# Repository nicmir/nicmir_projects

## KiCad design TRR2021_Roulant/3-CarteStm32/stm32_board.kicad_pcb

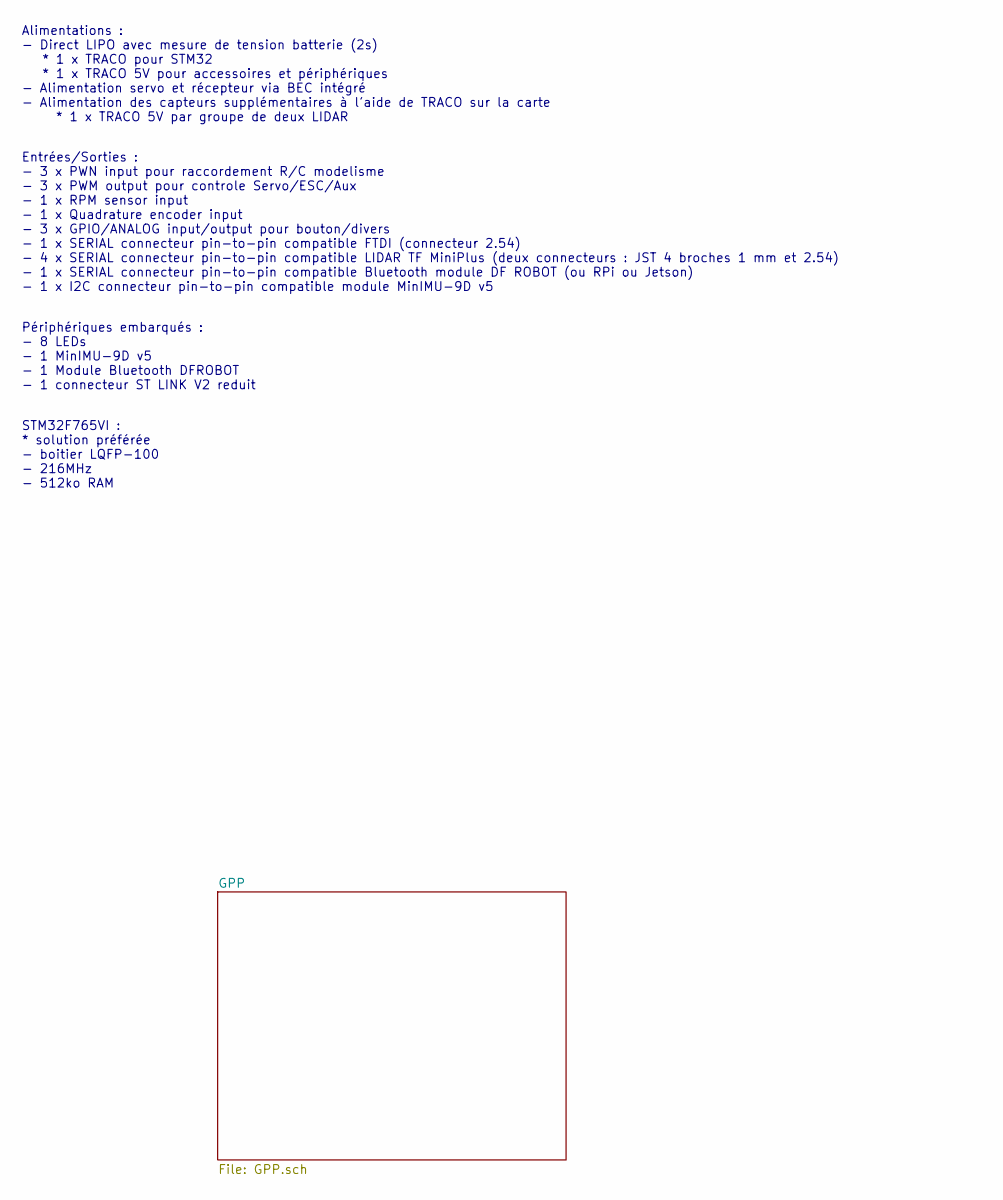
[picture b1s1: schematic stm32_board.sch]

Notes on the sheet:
Alimentations : - Direct LIPO avec mesure de tension batterie (2s) * 1 x TRACO pour STM32 * 1 x TRACO 5V pour accessoires et périphériques - Alimentation servo et récepteur via BEC intégré - Alimentation des capteurs supplémentaires à l'aide de TRACO sur la carte * 1 x TRACO 5V par groupe de deux L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
Entrées/Sorties : - 3 x PWN input pour raccordement R/C modelisme - 3 x PWM output pour controle Servo/ESC/Aux - 1 x RPM sensor input - 1 x Quadrature encoder input - 3 x GPIO/ANALOG input/output pour bouton/divers - 1 x SERIAL connecteur pin-to-pin compatible FTDI (connecteur 2.54) - 4 x SERIAL co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
Périphériques embarqués : - 8 LEDs - 1 MinIMU-9D v5 - 1 Module Bluetooth DFROBOT - 1 connecteur ST LINK V2 reduit
STM32F765VI : * solution préférée - boitier LQFP-100 - 216MHz - 512ko RAM

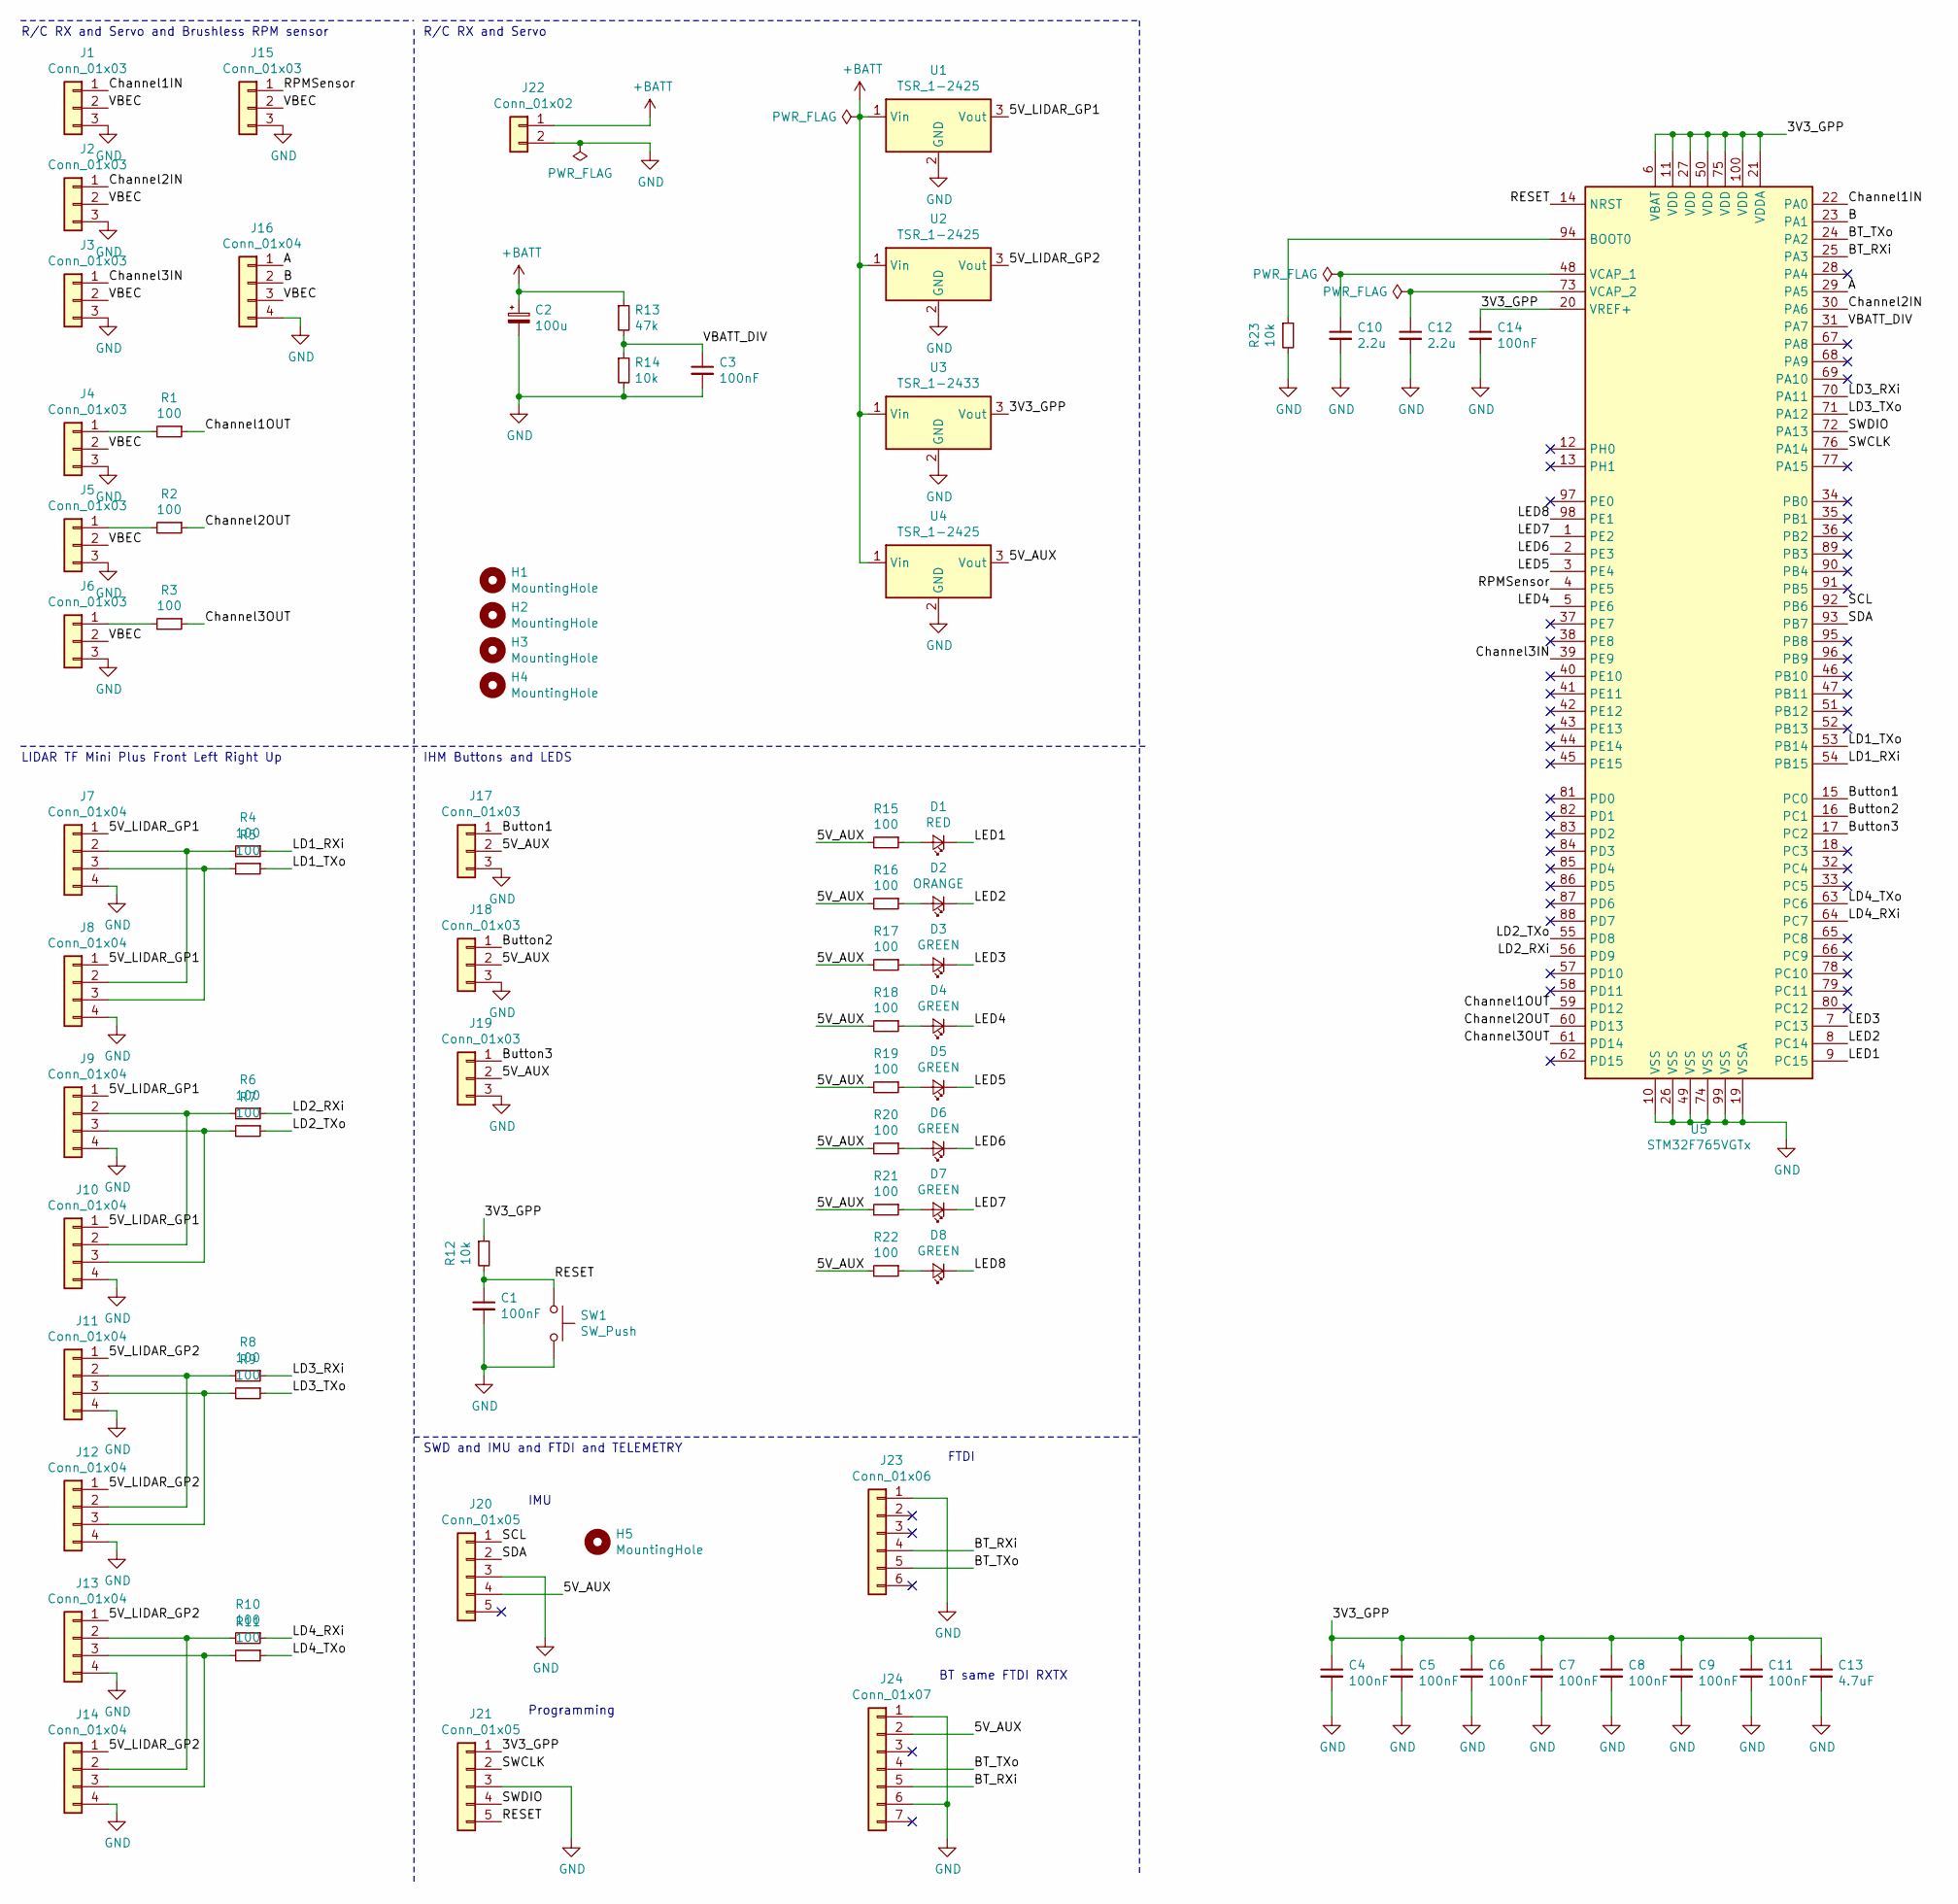
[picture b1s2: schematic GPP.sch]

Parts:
C1, C3, C4, C5, C6, C7, C8, C9, C11, C14: 100nF; C_0603_1608Metric_Pad1.05x0.95mm_HandSolder
C2: 100u; CP_Elec_8x6.9
C10, C12: 2.2u; C_0603_1608Metric_Pad1.05x0.95mm_HandSolder
C13: 4.7uF; C_0603_1608Metric_Pad1.05x0.95mm_HandSolder
D1: RED; LED_0805_2012Metric_Pad1.15x1.40mm_HandSolder
D2: ORANGE; LED_0805_2012Metric_Pad1.15x1.40mm_HandSolder
D3, D4, D5, D6, D7, D8: GREEN; LED_0805_2012Metric_Pad1.15x1.40mm_HandSolder
H1, H2, H3, H4, H5: MountingHole; MountingHole_3.2mm_M3
J1, J2, J3, J4, J5, J6, J15, J17, J18, J19: Conn_01x03; PinHeader_1x03_P2.54mm_Vertical
J7, J9, J11, J13: Conn_01x04; JST_SH_BM04B-SRSS-TB_1x04-1MP_P1.00mm_Vertical
J8, J10, J12, J14, J16: Conn_01x04; PinHeader_1x04_P2.54mm_Vertical
J20, J21: Conn_01x05; PinHeader_1x05_P2.54mm_Vertical
J22: Conn_01x02; PinHeader_1x02_P2.54mm_Vertical
J23: Conn_01x06; PinHeader_1x06_P2.54mm_Vertical
J24: Conn_01x07; PinHeader_1x07_P2.54mm_Vertical
R1, R2, R3, R4, R5, R6, R7, R8, R9, R10, R11, R15, R16, R17, R18, R19, R20, R21, R22: 100; R_0603_1608Metric_Pad1.05x0.95mm_HandSolder
R12, R14, R23: 10k; R_0603_1608Metric_Pad1.05x0.95mm_HandSolder
R13: 47k; R_0603_1608Metric_Pad1.05x0.95mm_HandSolder
SW1: SW_Push; SW_PUSH_6mm
U1, U2, U4: TSR_1-2425; Converter_DCDC_TRACO_TSR-1_THT
U3: TSR_1-2433; Converter_DCDC_TRACO_TSR-1_THT
U5: STM32F765VGTx; LQFP-100_14x14mm_P0.5mm

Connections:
+BATT: C2.1, J22.1, R13.1, U1.1 (Vin), U2.1 (Vin), U3.1 (Vin), U4.1 (Vin)
/GPP/3V3_GPP: C4.1, C5.1, C6.1, C7.1, C8.1, C9.1, C11.1, C13.1, C14.1, J21.1, R12.1, U3.3 (Vout), U5.6 (VBAT), U5.11 (VDD), U5.20 (VREF+), U5.21 (VDDA), U5.27 (VDD), U5.50 (VDD), U5.75 (VDD), U5.100 (VDD)
/GPP/5V_AUX: J17.2, J18.2, J19.2, J20.4, J24.2, R15.2, R16.2, R17.2, R18.2, R19.2, R20.2, R21.2, R22.2, U4.3 (Vout)
/GPP/5V_LIDAR_GP1: J7.1, J8.1, J9.1, J10.1, U1.3 (Vout)
/GPP/5V_LIDAR_GP2: J11.1, J12.1, J13.1, J14.1, U2.3 (Vout)
/GPP/A: J16.1, U5.29 (PA5)
/GPP/B: J16.2, U5.23 (PA1)
/GPP/BT_RXi: J23.4, J24.5, U5.25 (PA3)
/GPP/BT_TXo: J23.5, J24.4, U5.24 (PA2)
/GPP/Button1: J17.1, U5.15 (PC0)
/GPP/Button2: J18.1, U5.16 (PC1)
/GPP/Button3: J19.1, U5.17 (PC2)
/GPP/Channel1IN: J1.1, U5.22 (PA0)
/GPP/Channel1OUT: R1.1, U5.59 (PD12)
/GPP/Channel2IN: J2.1, U5.30 (PA6)
/GPP/Channel2OUT: R2.1, U5.60 (PD13)
/GPP/Channel3IN: J3.1, U5.39 (PE9)
/GPP/Channel3OUT: R3.1, U5.61 (PD14)
/GPP/LD1_RXi: R4.1, U5.54 (PB15)
/GPP/LD1_TXo: R5.1, U5.53 (PB14)
/GPP/LD2_RXi: R6.1, U5.56 (PD9)
/GPP/LD2_TXo: R7.1, U5.55 (PD8)
/GPP/LD3_RXi: R8.1, U5.70 (PA11)
/GPP/LD3_TXo: R9.1, U5.71 (PA12)
/GPP/LD4_RXi: R10.1, U5.64 (PC7)
/GPP/LD4_TXo: R11.1, U5.63 (PC6)
/GPP/LED1: D1.1 (K), U5.9 (PC15)
/GPP/LED2: D2.1 (K), U5.8 (PC14)
/GPP/LED3: D3.1 (K), U5.7 (PC13)
/GPP/LED4: D4.1 (K), U5.5 (PE6)
/GPP/LED5: D5.1 (K), U5.3 (PE4)
/GPP/LED6: D6.1 (K), U5.2 (PE3)
/GPP/LED7: D7.1 (K), U5.1 (PE2)
/GPP/LED8: D8.1 (K), U5.98 (PE1)
/GPP/RESET: C1.1, J21.5, R12.2, SW1.1, U5.14 (NRST)
/GPP/RPMSensor: J15.1, U5.4 (PE5)
/GPP/SCL: J20.1, U5.92 (PB6)
/GPP/SDA: J20.2, U5.93 (PB7)
/GPP/SWCLK: J21.2, U5.76 (PA14)
/GPP/SWDIO: J21.4, U5.72 (PA13)
/GPP/VBATT_DIV: C3.1, R13.2, R14.1, U5.31 (PA7)
/GPP/VBEC: J1.2, J2.2, J3.2, J4.2, J5.2, J6.2, J15.2, J16.3
GND: C1.2, C2.2, C3.2, C4.2, C5.2, C6.2, C7.2, C8.2, C9.2, C10.2, C11.2, C12.2, C13.2, C14.2, J1.3, J2.3, J3.3, J4.3, J5.3, J6.3, J7.4, J8.4, J9.4, J10.4, J11.4, J12.4, J13.4, J14.4, J15.3, J16.4, J17.3, J18.3, J19.3, J20.3, J21.3, J22.2, J23.1, J24.1, J24.6, R14.2, R23.2, SW1.2, U1.2 (GND), U2.2 (GND), U3.2 (GND), U4.2 (GND), U5.10 (VSS), U5.19 (VSSA), U5.26 (VSS), U5.49 (VSS), U5.74 (VSS), U5.99 (VSS)
unnamed: C10.1, U5.48 (VCAP_1)
unnamed: C12.1, U5.73 (VCAP_2)
unnamed: D1.2 (A), R15.1
unnamed: D2.2 (A), R16.1
unnamed: D3.2 (A), R17.1
unnamed: D4.2 (A), R18.1
unnamed: D5.2 (A), R19.1
unnamed: D6.2 (A), R20.1
unnamed: D7.2 (A), R21.1
unnamed: D8.2 (A), R22.1
unnamed: J4.1, R1.2
unnamed: J5.1, R2.2
unnamed: J6.1, R3.2
unnamed: J7.2, J8.2, R4.2
unnamed: J7.3, J8.3, R5.2
unnamed: J9.2, J10.2, R6.2
unnamed: J9.3, J10.3, R7.2
unnamed: J11.2, J12.2, R8.2
unnamed: J11.3, J12.3, R9.2
unnamed: J13.2, J14.2, R10.2
unnamed: J13.3, J14.3, R11.2
unnamed: R23.1, U5.94 (BOOT0)

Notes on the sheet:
LIDAR TF Mini Plus Front Left Right Up
R/C RX and Servo and Brushless RPM sensor
R/C RX and Servo
IHM Buttons and LEDS
SWD and IMU and FTDI and TELEMETRY
Programming
IMU
BT same FTDI RXTX
FTDI

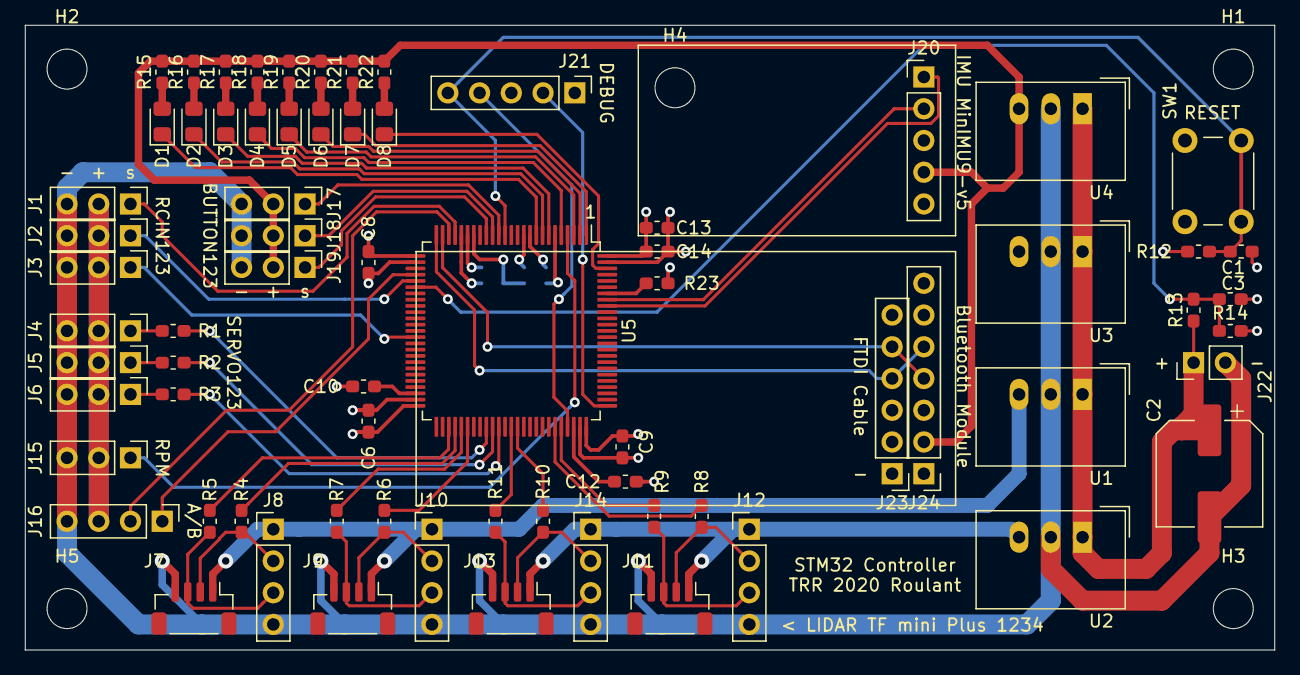
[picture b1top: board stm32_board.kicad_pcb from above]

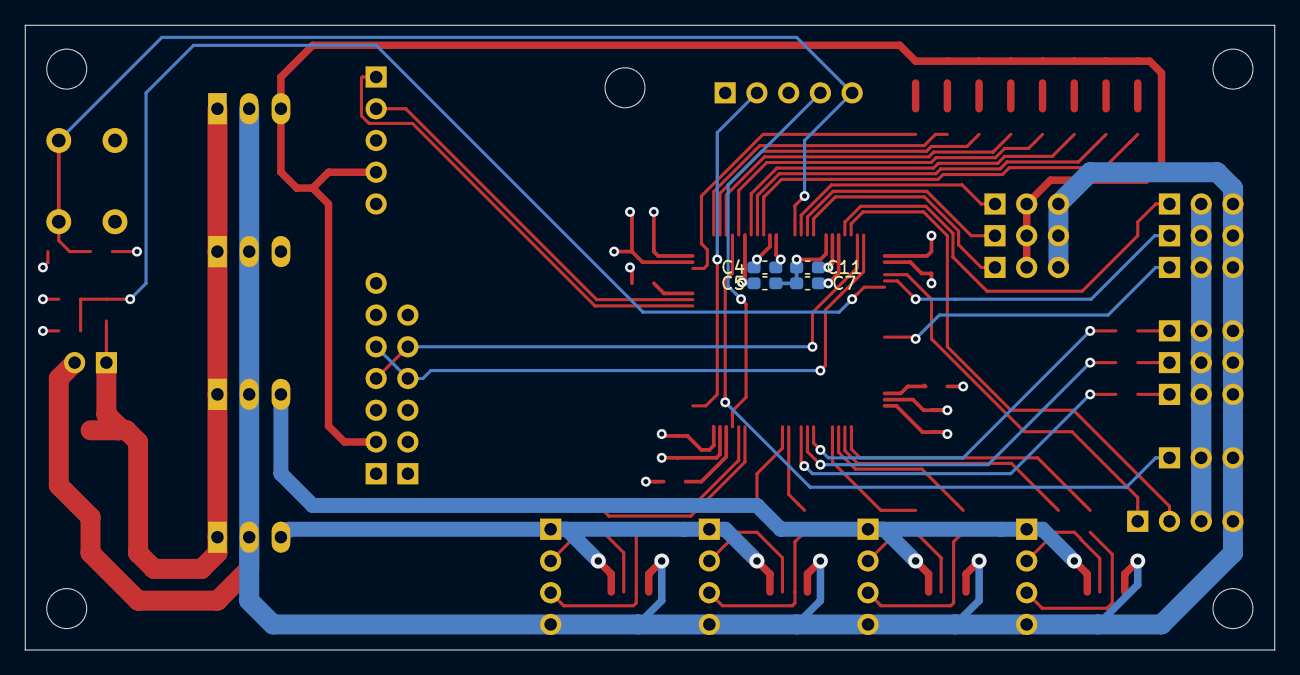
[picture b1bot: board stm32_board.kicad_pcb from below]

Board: 4 copper layers, 100.0 x 50.0 mm, 80 parts (4 on the bottom side), 65 nets.

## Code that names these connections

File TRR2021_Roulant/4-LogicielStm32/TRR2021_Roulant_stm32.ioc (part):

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Mcu.Name=STM32F756ZGTx
Mcu.Package=LQFP144
Mcu.UserName=STM32F756ZGTx
PA0/WKUP.GPIOParameters=GPIO_PuPd,GPIO_Label
PA0/WKUP.GPIO_Label=lid1_txd
PA0/WKUP.GPIO_PuPd=GPIO_PULLUP
PA0/WKUP.Mode=Asynchronous
PA0/WKUP.Signal=UART4_TX
PA1.GPIOParameters=GPIO_PuPd,GPIO_Label
PA1.GPIO_Label=lid1_rxd
PA1.GPIO_PuPd=GPIO_PULLUP
PA1.Mode=Asynchronous
PA1.Signal=UART4_RX
PA10.GPIOParameters=GPIO_Label
PA10.GPIO_Label=lid4_rxd
PA10.Mode=Asynchronous
PA10.Signal=USART1_RX
PA13.Signal=SYS_JTMS-SWDIO
PA14.Signal=SYS_JTCK-SWCLK
PA15.GPIOParameters=GPIO_Label
PA15.GPIO_Label=lid4_pwr_en
PA15.Signal=GPIO_Output
PA2.GPIOParameters=GPIO_Speed,GPIO_Label
PA2.GPIO_Label=tele_txd
PA2.GPIO_Speed=GPIO_SPEED_FREQ_LOW
PA2.Mode=Asynchronous
PA2.Signal=USART2_TX
PA3.GPIOParameters=GPIO_Speed,GPIO_Label
PA3.GPIO_Label=tele_rxd
PA3.GPIO_Speed=GPIO_SPEED_FREQ_LOW
PA3.Mode=Asynchronous
PA3.Signal=USART2_RX
PA4.GPIOParameters=GPIO_Label
PA4.GPIO_Label=Vbatt
PA4.Signal=ADCx_IN4
PA5.GPIOParameters=GPIO_Label
PA5.GPIO_Label=SpeedIn
PA5.Signal=S_TIM2_CH1_ETR
PA6.GPIOParameters=GPIO_Label
PA6.GPIO_Label=DirIn
PA6.Signal=S_TIM3_CH1
PA7.GPIOParameters=GPIO_Label
PA7.GPIO_Label=Vesc
PA7.Signal=ADCx_IN7
PA9.GPIOParameters=GPIO_Label
PA9.GPIO_Label=lid4_txd
PA9.Mode=Asynchronous
PA9.Signal=USART1_TX
PB0.GPIOParameters=GPIO_Label
PB0.GPIO_Label=qtr_ch2
PB0.Signal=ADCx_IN8
PB1.GPIOParameters=GPIO_Label
PB1.GPIO_Label=qtr_ch1
PB1.Signal=ADCx_IN9
PB10.GPIOParameters=GPIO_Label
PB10.GPIO_Label=lid3_txd
PB10.Mode=Asynchronous
PB10.Signal=USART3_TX
PB11.GPIOParameters=GPIO_Label
PB11.GPIO_Label=lid3_rxd
PB11.Mode=Asynchronous
PB11.Signal=USART3_RX
PB12.GPIOParameters=GPIO_Label
PB12.GPIO_Label=lid2_pwr_en
PB12.Signal=GPIO_Output
PB13.GPIOParameters=GPIO_Label
PB13.GPIO_Label=lid3_pwr_en
PB13.Signal=GPIO_Output
PB14.GPIOParameters=GPIO_Label
PB14.GPIO_Label=SpeedSensor
PB14.Signal=S_TIM12_CH1
PB2.GPIOParameters=GPIO_Label
PB2.GPIO_Label=lid1_pwr_en
PB2.Signal=GPIO_Output
PB5.GPIOParameters=GPIO_Label
PB5.GPIO_Label=cmdLeds
PB5.Signal=GPIO_Output
PB6.Mode=I2C
PB6.Signal=I2C1_SCL
PB7.Mode=I2C
PB7.Signal=I2C1_SDA
PC0.GPIOParameters=GPIO_Label
PC0.GPIO_Label=qtr_ch8
PC0.Signal=ADCx_IN10
PC1.GPIOParameters=GPIO_Label
PC1.GPIO_Label=qtr_ch7
PC1.Signal=ADCx_IN11
PC10.GPIOParameters=GPIO_Label
PC10.GPIO_Label=lid5_pwr_en
PC10.Signal=GPIO_Output
PC12.GPIOParameters=GPIO_PuPd,GPIO_Label
PC12.GPIO_Label=lid5_txd
PC12.GPIO_PuPd=GPIO_PULLUP
PC12.Mode=Asynchronous
PC12.Signal=UART5_TX
PC2.GPIOParameters=GPIO_Label
PC2.GPIO_Label=qtr_ch6
PC2.Signal=ADCx_IN12
PC3.GPIOParameters=GPIO_Label
PC3.GPIO_Label=qtr_ch5
PC3.Signal=ADCx_IN13
PC4.GPIOParameters=GPIO_Label
PC4.GPIO_Label=qtr_ch4
PC4.Signal=ADCx_IN14
PC5.GPIOParameters=GPIO_Label
PC5.GPIO_Label=qtr_ch3
PC5.Signal=ADCx_IN15
PD12.GPIOParameters=GPIO_PuPd,GPIO_Label
PD12.GPIO_Label=SpareIn
PD12.GPIO_PuPd=GPIO_PULLUP
PD12.Signal=S_TIM4_CH1
PD15.GPIOParameters=GPIO_Label
PD15.GPIO_Label=Spare7
PD15.Signal=GPIO_Output
PD2.GPIOParameters=GPIO_PuPd,GPIO_Label
PD2.GPIO_Label=lid5_rxd
PD2.GPIO_PuPd=GPIO_PULLUP
PD2.Mode=Asynchronous
PD2.Signal=UART5_RX
PD4.GPIOParameters=GPIO_Label
PD4.GPIO_Label=boutonExt1
PD4.Signal=GPIO_Input
PD5.GPIOParameters=GPIO_Label
PD5.GPIO_Label=boutonExt2
PD5.Signal=GPIO_Input
PD6.GPIOParameters=GPIO_Label
PD6.GPIO_Label=led3
PD6.Signal=GPIO_Output
PD7.GPIOParameters=GPIO_Label
PD7.GPIO_Label=led2
PD7.Signal=GPIO_Output
PE0.GPIOParameters=GPIO_PuPd,GPIO_Label
PE0.GPIO_Label=lid6_rxd
PE0.GPIO_PuPd=GPIO_PULLUP
PE0.Mode=Asynchronous
PE0.Signal=UART8_RX
PE1.GPIOParameters=GPIO_PuPd,GPIO_Label
PE1.GPIO_Label=lid6_txd
PE1.GPIO_PuPd=GPIO_PULLUP
PE1.Mode=Asynchronous
PE1.Signal=UART8_TX
PE11.GPIOParameters=GPIO_Label
PE11.GPIO_Label=DirOut
PE11.Signal=S_TIM1_CH2
PE13.GPIOParameters=GPIO_Label
PE13.GPIO_Label=SpareOut
PE13.Signal=S_TIM1_CH3
PE7.GPIOParameters=GPIO_PuPd,GPIO_Label
PE7.GPIO_Label=lid2_rxd
PE7.GPIO_PuPd=GPIO_PULLUP
PE7.Mode=Asynchronous
PE7.Signal=UART7_RX
PE8.GPIOParameters=GPIO_PuPd,GPIO_Label
PE8.GPIO_Label=lid2_txd
PE8.GPIO_PuPd=GPIO_PULLUP
PE8.Mode=Asynchronous
PE8.Signal=UART7_TX
PE9.GPIOParameters=GPIO_Label
PE9.GPIO_Label=SpeedOut
PE9.Signal=S_TIM1_CH1
PF10.GPIOParameters=GPIO_Label
PF10.GPIO_Label=qtr_ch9
PF10.Mode=IN8
PF10.Signal=ADC3_IN8
PF11.GPIOParameters=GPIO_Label
PF11.GPIO_Label=lid6_pwr_en
PF11.Signal=GPIO_Output
PF3.GPIOParameters=GPIO_Label
PF3.GPIO_Label=qtr_ch16
PF3.Mode=IN9
PF3.Signal=ADC3_IN9
PF4.GPIOParameters=GPIO_Label
PF4.GPIO_Label=qtr_ch15
PF4.Mode=IN14
PF4.Signal=ADC3_IN14
PF5.GPIOParameters=GPIO_Label
PF5.GPIO_Label=qtr_ch14
PF5.Mode=IN15
PF5.Signal=ADC3_IN15
PF6.GPIOParameters=GPIO_Label
PF6.GPIO_Label=qtr_ch13
PF6.Mode=IN4
PF6.Signal=ADC3_IN4
PF7.GPIOParameters=GPIO_Label
PF7.GPIO_Label=qtr_ch12
PF7.Mode=IN5
PF7.Signal=ADC3_IN5
PF8.GPIOParameters=GPIO_Label
PF8.GPIO_Label=qtr_ch11
PF8.Mode=IN6
PF8.Signal=ADC3_IN6
PF9.GPIOParameters=GPIO_Label
PF9.GPIO_Label=qtr_ch10
PF9.Mode=IN7
PF9.Signal=ADC3_IN7
PG10.GPIOParameters=GPIO_Label
PG10.GPIO_Label=bouton3
PG10.Signal=GPIO_Input
PG11.GPIOParameters=GPIO_Label
PG11.GPIO_Label=bouton2
PG11.Signal=GPIO_Input
PG12.GPIOParameters=GPIO_Label
PG12.GPIO_Label=bouton1
PG12.Signal=GPIO_Input
PG2.GPIOParameters=GPIO_Label
PG2.GPIO_Label=Spare6
PG2.Signal=GPIO_Output
PG3.GPIOParameters=GPIO_Label
PG3.GPIO_Label=Spare5
PG3.Signal=GPIO_Output
PG4.GPIOParameters=GPIO_Label
PG4.GPIO_Label=Spare4
PG4.Signal=GPIO_Output
PG5.GPIOParameters=GPIO_Label
PG5.GPIO_Label=Spare3
PG5.Signal=GPIO_Output
PG6.GPIOParameters=GPIO_Label
PG6.GPIO_Label=Spare2
PG6.Signal=GPIO_Output
PG7.GPIOParameters=GPIO_Label
PG7.GPIO_Label=Spare1
PG7.Signal=GPIO_Output
PG8.GPIOParameters=GPIO_Label
PG8.GPIO_Label=Spare0
PG8.Signal=GPIO_Output
PG9.GPIOParameters=GPIO_Label
PG9.GPIO_Label=led1
PG9.Signal=GPIO_Output
PH0/OSC_IN.GPIOParameters=GPIO_Label
PH0/OSC_IN.GPIO_Label=qtr_ctrl_odd
PH0/OSC_IN.Signal=GPIO_Output
PH1/OSC_OUT.GPIOParameters=GPIO_Label
PH1/OSC_OUT.GPIO_Label=qtr_ctrl_even
PH1/OSC_OUT.Signal=GPIO_Output
RCC.HSE_VALUE=25000000
RCC.SYSCLKFreq_VALUE=216000000
RCC.SYSCLKSource=RCC_SYSCLKSOURCE_PLLCLK
board=custom

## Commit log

2021-08-29 KickOff
2021-10-17 Schematic Update
2021-11-01 1ere version soft
2021-12-26 fin couches basses
2022-01-09 télémétrie et algo découverte
2023-04-02 Télécommande
